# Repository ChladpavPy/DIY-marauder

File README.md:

# DIY Marauder

I have made this project because it was my first ever pcb project and I started with blueprint, I wanted something cool looking, like pentesting device for ethical hacking and as a experimental gadget that I could programm whatever way I wanted to do something cool and finally bring the code to life.

A custom macro keypad / pentesting node based on the Seeed XIAO ESP32S3 (originally designed for RP2040). Designed in KiCad and Fusion 360.

## Project Features

* **Microcontroller:** Seeed XIAO ESP32S3 (USB-C) *(Swapped from RP2040 due to delivery issues)*
* **Display:** 0.96" OLED (I2C) *(Swapped from 0.91")*
* **Controls:** 1x EC11 Rotary Encoder + 2x Mechanical MX Switches
* **Case:** Custom 3D printed snap-fit enclosure

## Gallery
### Build Preview

### Schematic

### PCB Routing

### 3D PCB Render

### 3D Printed Case

### Assembly Preview
The PCB fits perfectly inside the custom 3D printed case (designed with 0.4mm clearance).

### Assembly Preview Seeed XIAO RP2040

---

Here is the updated BOM, previously I would have used XIAO RP2040, but since there was that customs delivery issues, I bought and used some of the remaining components from zeropad project

## Bill of Materials (BOM)

| Component | Qty | Purpose / Description | Price (USD) | Link / Distributor |
| :--- | :---: | :--- | :--- | :--- |
| **Seeed XIAO ESP32S3** | 1 | Microcontroller (Used instead of RP2040 due to delivery issues). | ~$7.50 | [Botland](https://botland.cz/moduly-wifi-a-bt-esp32/22878-seeed-xiao-esp32-s3-wifi-bluetooth-seeedstudio-113991114.html) |
| **0.96" I2C OLED Display** | 1 | Screen to show UI and analysis data (Swapped from 0.91"). | ~$2.00 | [AliExpress](https://a.aliexpress.com/_EGSrJ7g) |
| **EC11 Rotary Encoder** | 1 | Navigation control with push button. | ~$1.50 | [SparkFun](https://www.sparkfun.com/products/9117) |
| **Cherry MX Switches** | 2 | Secondary input buttons (Sourced from previous build). | ~$6.08 | [AliExpress](https://a.aliexpress.com/_EuLENRY) |
| **1U Blank Keycaps** | 2 | Standard covers for the mechanical switches. | ~$3.35 | [AliExpress](https://a.aliexpress.com/_Eyx6JJo) |
| **Knob** | 1 | Cap for the rotary encoder. | ~$1.50 | [SparkFun](https://www.sparkfun.com/products/10597) |
| **3D Printed Case** | 1 | Enclosure. Files in `3D_Models` folder. | $0.00 | printing legion |

---

## Folder Structure
* **Gerbers:** Manufacturing files ready for JLCPCB.
* **KiCad_Source:** Editable project files for KiCad.
* **3D_Models:** STL and STEP files for printing.

Journals - 
I am really sorry for the confusion, I thought that I was just submitting it for design review at first in stasis and I noticed it just now, however somehow it shows that it was submitted for build review, so I am adding the journals that I wanted to write in stasis there with time - I hope that it will be okay like this and also thank you for the review! : Journals - 

1. journal - soldering and first testing - 4 hours

Before that I have obviously spent a lot of time witch searching the cheapest esp32s3 xiao, which I could get, since these devices were not exatly cheap in czech republic or aliexpress and also wrote some firmware even before that although I still have not it working because I was still missing the keycaps and cherry mx switches which I used from the zeropad projet which arrived on monday, so I still had some time to build it.
I started by soldering everything. First I soldered the esp32-s3, but then I hit some major issues. I was struggling with how to mount the Cherry MX switches because the enclosure was so high and I needed them fixed at the top. It eventually hit me I could just place the switches in that top space and connect them from the bottom using jumper wires through the tht pads. So I soldered pin headers to the pcb on the bottom and then I soldered female jumpers to the switches and connected them. I did that twice.
After that I ran into another problem. Because of the postal service I did not have the encoder I ordered so I tried to scavenge one from around the house. I spent forever searching through the garage until I finally realized I could grab an encoder from an old grill. Finding the screwdriver to open it up in that messy garage was not easy but I managed to dismantle it only to realize it did not have any pins so it was absolutely useless. I just wasted my time.
Anyway I managed to get the display working. I used a pin header on the pcb and connected the screen via jumpers. After the hardware was somewhat assembled I had to actually make it do something useful. I did not want this to be just a simple script I wanted a standalone tool for network analysis. Since my plan to use a scavenged grill encoder failed I had to rely entirely on the two Cherry MX switches. This meant I could not just use a standard library for the menu so I had to write a custom UI system from scratch. I built a scrollable menu interface that dynamically adjusts to the oled screen. Writing a state machine for the button debouncing to handle both short and long presses took way more time than I expected but it was necessary to make the navigation feel responsive.
The firmware itself is around 1100 lines of c++ code. I implemented a wifi scanner and analyzer that scans 2.4ghz bands grabs rssi encryption types and mac addresses. I even added a visual channel analyzer to see where the interference is. Then I added a ble scanner to find bluetooth devices around and sort them by signal strength. Since this is meant to be portable I also implemented a deep sleep mode to save power when it is not actively scanning. Getting the display library to play nice with the specific i2c pins i routed on my pcb required some tweaking but once the display initialized it was satisfying.
Looking back considering this was my first pcb I did some pretty stupid things. I have no idea what I was thinking. First off I did not even realize i could use a gnd filled zone or plane so I just routed gnd traces everywhere but whatever it works. The real problem was the 3d case. For some reason I made a circular hole for the usb-c port not realizing I needed to fit the whole connector through it not just the cable. I literally just made a hole for the cable. Plus I placed the xiao in the middle of the board instead of at the edge so the usb-c port does not stick out properly which looks weird.
I had to fix the hole somehow. I tried sandpaper but that would have taken hours so I went for the radical solution. I grabbed a soldering iron and just ugly-melted the opening bigger despite breathing in all those plastic fumes. It did the trick and the cable fits now. Obviously I did not use my good soldering iron for that just an old destroyed one that was a year old anyway so it does not really matter.
Looking at the final build it is definitely a prototype. The hot glue and the missing encoder do not look professional but the core engineering is solid. I designed the pcb figured out the mechanical mounting for the switches and wrote a custom os for it. It works as a pocket-sized pentesting node. That wrapped up the soldering and assembly. I then started programming and testing the board but I will write about that in the next journal entry.

2. journal - writing the firmware and flashing the device - 4 hours 20 minutes
After the hardware was somehow assembled, I had to actually make it do something useful. I did not want this to be just a simple script, I wanted a standalone tool for network analysis. Since my plan to use a scavenged grill encoder failed, I had to rely entirely on the two Cherry MX switches. This meant I could not just use a standard library for the menu, so I had to write a custom UI system from scratch. I built a scrollable menu interface that dynamically adjusts to the OLED screen. Writing a state machine for the button debouncing to handle both short and long presses took way more time than I expected, but it was necessary to make the navigation feel responsive.
The firmware itself is around 1100 lines of C++ code. I implemented a WiFi scanner and analyzer that scans 2.4GHz bands, grabs RSSI, encryption types and MAC addresses. I even added a visual channel analyzer to see where the interference is. Then I added a BLE scanner to find Bluetooth devices around and sort them by signal strength. Since this is meant to be portable, I also implemented a deep sleep mode to save power when it is not actively scanning. Getting the display library to play nice with the specific I2C pins I routed on my PCB required some tweaking, but once the display initialized, it was incredibly satisfying. Looking at the final build, it is definitely a prototype. The hot glue and the missing encoder do not look exactly professional, but the core engineering is solid. I designed the PCB, figured out the mechanical mounting for the switches, and wrote a completely custom OS for it. It works good as a pocket sized pentesting device and even integrated a encoder detection system since I have not got encoder to make it work although I dont have it. I am actually also really amazed what you can actually do with just a esp32 with just 7 pins and also with small 0.96 inch display

also regarding the BOM in readme I did not have there links before since it should have been shipped from hacklub HQ, but actually updated them and added them because I have used different parts, which was caused by the delivery problems, the only difference would be probably just the performance and that I would not have access to wifi functions with RP2040 otherwise the firmware should be suitable for both devices. - this was a HACKPAD

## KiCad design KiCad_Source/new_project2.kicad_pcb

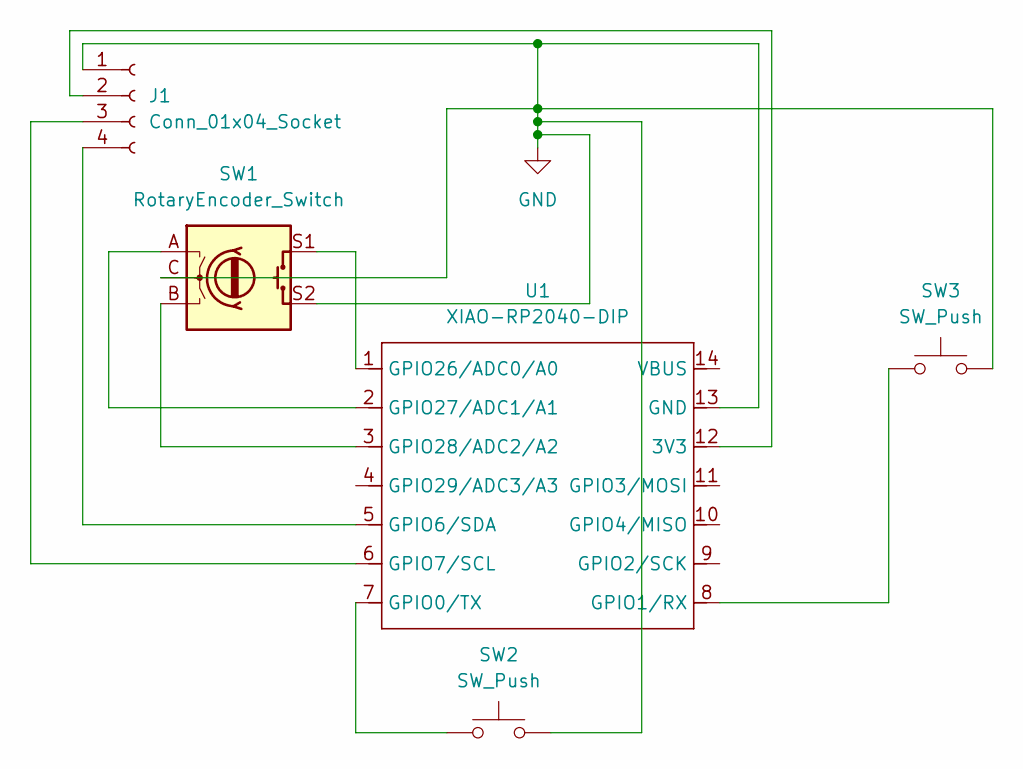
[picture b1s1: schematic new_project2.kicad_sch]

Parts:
J1: Conn_01x04_Socket; PinHeader_1x04_P2.54mm_Vertical
SW1: RotaryEncoder_Switch; RotaryEncoder_Alps_EC11E-Switch_Vertical_H20mm
SW2, SW3: SW_Push; SW_Cherry_MX_1.00u_PCB
U1: XIAO-RP2040-DIP

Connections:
GND: J1.1, SW1.C, SW1.S2, SW2.2, SW3.1, U1.13 (GND)
unnamed: J1.2, U1.12 (3V3)
unnamed: J1.3, U1.6 (GPIO7/SCL)
unnamed: J1.4, U1.5 (GPIO6/SDA)
unnamed: SW2.1, U1.7 (GPIO0/TX)
unnamed: SW3.2, U1.8 (GPIO1/RX)
unnamed: SW1.S1, U1.1 (GPIO26/ADC0/A0)
unnamed: SW1.A, U1.2 (GPIO27/ADC1/A1)
unnamed: SW1.B, U1.3 (GPIO28/ADC2/A2)

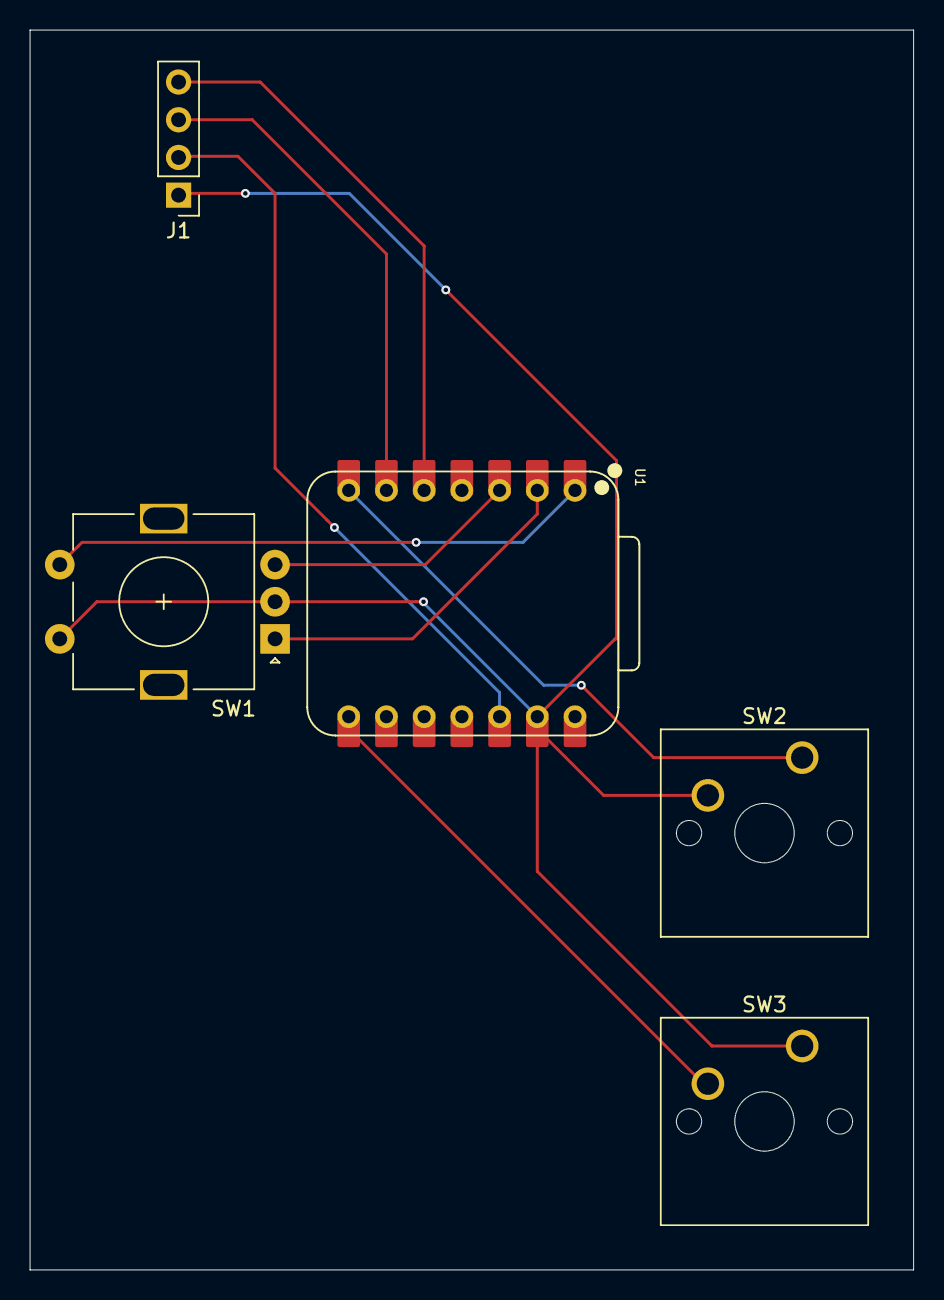
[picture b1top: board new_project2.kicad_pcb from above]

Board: 2 copper layers, 59.5 x 83.5 mm, 5 parts (0 on the bottom side), 9 nets.

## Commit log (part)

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2026-01-19 PCB schematic kicad
2026-01-19 marauder_master
    contains gbr and gbrjob files and the pdf schematic
2026-01-21 Add assembly preview to README
    Added assembly preview section with images.
